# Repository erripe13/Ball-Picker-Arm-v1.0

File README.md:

#  Bras Robotisé attrapeur de balles

Ce projet est un bras robotisé classique à deux axes + une pince, destiné à attraper une balle grâce à une vision basée sur OpenCV.
Ce repository contient l'ensemble du code source ainsi que la CAO du shield Arduino.

## Principe et matériel

Ce projet est basé sur un **Raspberry Pi 4** (2GB RAM) muni de sa **Pi Caméra v2**, exécutant le code Python pour la détection de la balle, et transmettant par USB à l'**Arduino** les coordonnées de cette balle. L'Arduino est chargée de commander le **moteur pas-à-pas** de translation et les deux **servomoteurs** de commande du bras robotisé de manière à ce qu'il attrape la balle en question.

Un Shield Arduino conçu pour ce projet, dont la CAO est disponible dans le dossier [Shield PCB](https://github.com/erripe13/Ball-Picker-Arm-v1.0/tree/main/Shield%20PCB).  Il permet de connecter à l'Arduino, mais surtout d'alimenter, tous les périphériques du projet (hormis la caméra, l'interrupteur DEBUG, et le ruban led qui sont directement connectés au Raspberry Pi) à savoir :
 - Capteur fin de course de translation (calibration de l'axe X)
 - Capteur de température (régulation de la ventilation) (5V)
 - Ventilateurs (12V input, sortie variable par pwm)
 - Servomoteur fort couple n°1 (6V)
 - Servomoteur fort couple n°2 (6V)
 - Servomoteur de la pince (5V)
 - Driver du moteur pas-à-pas (12V)

Ce Shield comporte aussi deux circuits de coupure d'alimentation des moteurs par deux MOSFET (n et p, IRL510 et IRF4905) en montage high-side. Cela permet de "reposer" les servomoteurs quand ils ne servent pas pour éviter la surchauffe. Un MOSFET-N est également utilisé en montage low-side pour réguler l'alimentation des ventilateurs. Les détails et la schématique de cette carte sont disponibles dans le dossier du projet KiCad précédemment cité.

## Rôle des programmes - arborescence du dépôt

À la racine sont disponibles les programmes Python destinés à être exécutés sur le Raspberry Pi. 

 - *ball_tracking* est le programme principal, il remplit les fonctions suivantes :
	 - détection de la balle par filtrage HSV puis détection de contours
	 - compensation de la perspective dûe à l'orientation non-zénitale de la caméra
	 - extraction des coordonnées réelles de la balle
	 - envoi des coordonnées à l'Arduino par USB une fois la balle immobile
 - *hsv_define* permet de définir manuellement les seuils (bas et haut) de chaque paramètre du filtre HSV (cf. tuto plus bas dans ce document)
 - *NeoPixel* est exécuté au démarrage du système et allume en blanc le ruban LED connecté au GPIO18 du Raspberry

Dans le dossier arduino_runrobot on trouve le programme unique exécuté par l'Arduino

 - *arm_arduino.ino* permet d'effectuer les tâches suivantes :
	 - réception de décodage des coordonnées de la balle
	 - pilotage des moteurs pour se déplacer et aller attraper la balle

## Procédure de calibration

### Calibration du trapèze de détection - correction de la perspective

La calibration de la correction de perspective a été réduite au plus simple. Pour y accéder, il faut démarrer le système avec le switch DEBUG activé. On dispose ainsi d'un affichage de la vidéo avant traitement :
L'objectif est de régler manuellement la position de la caméra pour faire coincider les points rouges avec les quatre angles du plateau de jeu. 

Une fois cette tâche réalisée on peut basculer le bouton debug en position normale et observer l'image après son traitement, par conséquent rectifiée.

Si on souhaite modifier les coordonnées de ces points (attention : ce n'est pas nécessaire dans la situation du modèle actuel du robot) il s'agit des lignes 70 à 75 du programme *ball_tracking* :

    #affichage des points rouges
    calib = cv2.circle(frame,(84,38), 5,(0,0,255),-1)
    calib = cv2.circle(calib,(449,36),5,(0,0,255),-1)
    calib = cv2.circle(calib,(34,419),5,(0,0,255),-1)
    calib = cv2.circle(calib,(517,415),5,(0,0,255),-1)
    #déclaration des points du trapèze à rectifier (identiques au points rouges, respecter l'ordre)
    imgPts = np.float32([[84,38],[449,36],[34,419],[517,415]])

### Calibration du filtre de couleur  - détection de la balle

Si la balle n'est pas correctement détectée, où qu'on souhaite utiliser une autre couleur de balle, il est nécessaire de trouver les 6 seuils de réglage du filtre.
Il faut exécuter le programme *hsv_define*. On y observe le flux caméra sans filtrage, puis une autre fenêtre avec 6 sliders et la sortie du filtre juste en-dessous.

Il faut d'abord cherche les 3 meilleurs paramètres LOW dans l'ordre HSV pour que la sortie du filtre soit la plus propre possible, puis ensuite diminuer les 3 paramètres HIGH pour nettoyer au mieux le reste de pollution. La sortie du filtre doit afficher en blanc la balle, quasiment sans aucune autre perturbation. Une fois ces 6 paramètres trouvés, il faut les renseigner dans le programme _ball_tracking_ au lignes 23 et 24.

    HSVLower = (15, 112, 143) #(H low, S low, V low)
    HSVUpper = (45, 255, 255) #(H up, S up, V up)

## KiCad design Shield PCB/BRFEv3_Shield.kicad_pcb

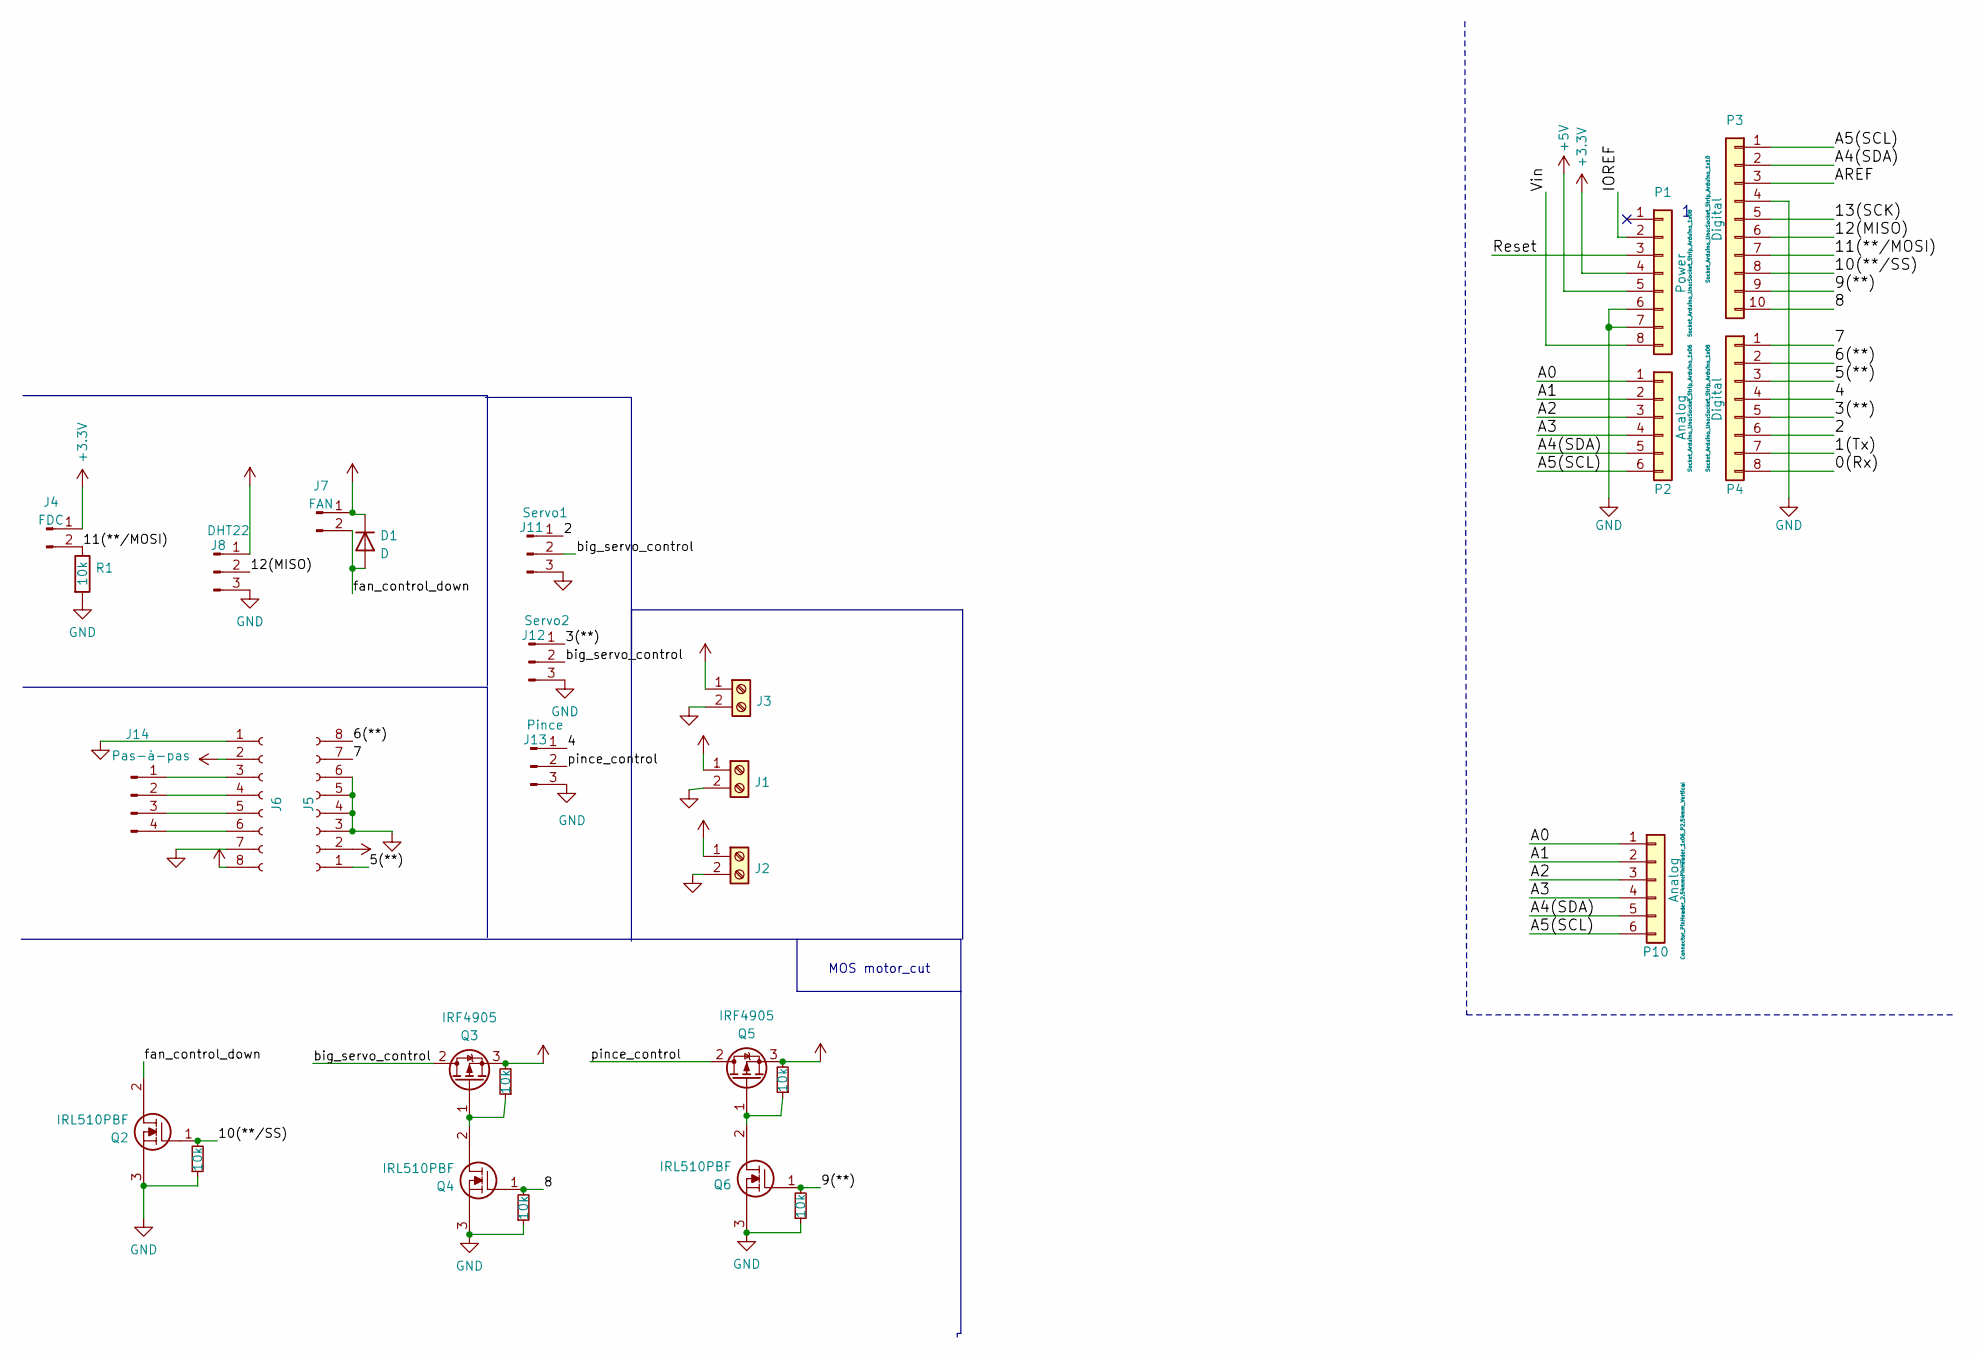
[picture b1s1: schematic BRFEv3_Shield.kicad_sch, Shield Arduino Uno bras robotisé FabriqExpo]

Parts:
D1: D; D_DO-41_SOD81_P3.81mm_Vertical_AnodeUp
J1, J2, J3: Screw_Terminal_01x02; PhoenixContact_MSTBVA_2,5_2-G_1x02_P5.00mm_Vertical
J4: FDC; PinHeader_1x02_P2.54mm_Vertical
J5, J6: Conn_01x08_Female; PinHeader_1x08_P2.54mm_Vertical
J7: FAN; PinHeader_1x02_P2.54mm_Vertical
J8: DHT22; PinHeader_1x03_P2.54mm_Vertical
J11: Servo1; PinHeader_1x03_P2.54mm_Vertical
J12: Servo2; PinHeader_1x03_P2.54mm_Vertical
J13: Pince; PinHeader_1x03_P2.54mm_Vertical
J14: Pas-à-pas; PinHeader_1x04_P2.54mm_Vertical
P1: Power; Socket_Strip_Arduino_1x08
P2: Analog; Socket_Strip_Arduino_1x06
P3: Digital; Socket_Strip_Arduino_1x10
P4: Digital; Socket_Strip_Arduino_1x08
P10: Analog; PinHeader_1x06_P2.54mm_Vertical
Q2, Q4, Q6: IRL510PBF; TO-220-3_Vertical; Manufacturer_Part_Number IRL510PBF; Mouser Part Number 844-IRL510PBF
Q3, Q5: IRF4905; TO-220-3_Vertical
R1, R3, R4, R5, R6, R7: 10k; R_Axial_DIN0204_L3.6mm_D1.6mm_P5.08mm_Vertical

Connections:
+3V3: J4.1, P1.4
+5V: J2.1, J5.2, J6.2, J8.1, P1.5, Q5.3 (S), R6.2
+6V: J1.1, Q3.3 (S), R4.2
+12V: D1.1 (K), J3.1, J6.8, J7.1
/0(Rx): P4.8
/1(Tx): P4.7
/2: J11.1, P4.6
/3(**): J12.1, P4.5
/4: J13.1, P4.4
/5(**): J5.1, P4.3
/6(**): J5.8, P4.2
/7: J5.7, P4.1
/8: P3.10, Q4.1, R5.2
/9(**): P3.9, Q6.1, R7.2
/12(MISO): J8.2, P3.6
/13(SCK): P3.5
/A0: P2.1, P10.1
/A1: P2.2, P10.2
/A2: P2.3, P10.3
/A3: P2.4, P10.4
/A4(SDA): P2.5, P3.2, P10.5
/A5(SCL): P2.6, P3.1, P10.6
/AREF: P3.3
/IOREF: P1.2
/Reset: P1.3
/Vin: P1.8
/big_servo_control: J11.2, J12.2, Q3.2 (D)
/fan_control_down: D1.2 (A), J7.2, Q2.2
/pince_control: J13.2, Q5.2 (D)
GND: J1.2, J2.2, J3.2, J5.3, J5.4, J5.5, J5.6, J6.1, J6.7, J8.3, J11.3, J12.3, J13.3, P1.6, P1.7, P3.4, Q2.3, Q4.3, Q6.3, R1.2, R3.1, R5.1, R7.1
unnamed: J6.3, J14.1
unnamed: J6.4, J14.2
unnamed: J6.5, J14.3
unnamed: J6.6, J14.4
unnamed: Q3.1 (G), Q4.2, R4.1
unnamed: Q5.1 (G), Q6.2, R6.1

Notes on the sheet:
MOS motor_cut

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
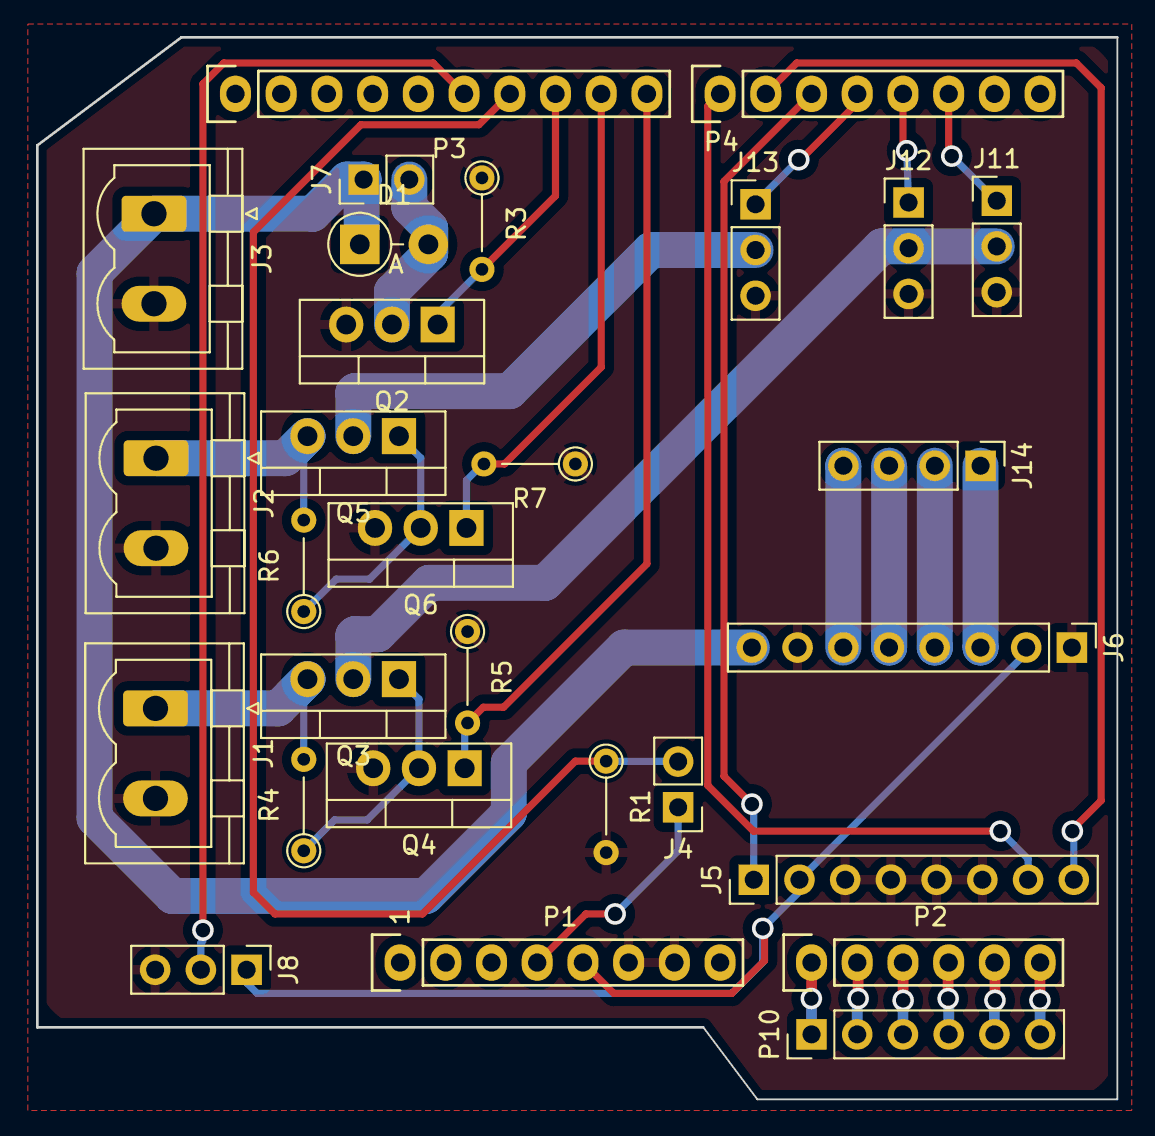
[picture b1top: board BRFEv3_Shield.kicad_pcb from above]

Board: 2 copper layers, 60.0 x 59.0 mm, 29 parts (0 on the bottom side), 31 nets.

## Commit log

2022-04-26 first push
    updated opencv and whole working code
2022-04-29 pi commit
2022-04-29 ball track
2022-05-10 gitignore
2022-05-11 +cao
2022-05-11 updatecao
2022-05-11 cao update
2022-05-11 update cao
2022-05-14 shield update
2022-05-14 Arduino script
2022-05-16 Arduino update
2022-05-16 update commentaires
2022-05-17 correction altium
2022-05-18 mise à jour gui test py3
2022-05-19 update programmes d'essai
2022-05-19 update calib distorsion
2022-05-19 update calib
2022-05-20 test
2022-05-20 test programs update
2022-05-24 update calib img
2022-05-24 up calib img
2022-05-24 calib up
2022-05-24 update correc arduino
2022-05-24 data disto
2022-05-24 update festival
2022-05-25 calib update
2022-05-25 update test mod
2022-05-25 mise au point
2022-05-28 upload calib
2022-05-28 pointloc
2022-05-28 capture
2022-05-28 updateperspec
2022-05-28 update calib intrisèque
2022-05-30 update arduino
2022-05-30 updatea rduino
2022-06-02 update general
2022-06-02 source main
2022-06-02 nouvelle proposition
2022-06-07 backup
2022-06-13 update servo offset
2022-06-13 update servo
2022-06-16 update shield
2022-06-17 update calib+cao
2022-06-17 calibopti
2022-06-20 update cao+calib
2022-06-23 add fancontrol
2022-06-23 added proportional fan control
2022-06-23 update new arm + RGB
2022-06-25 wqsx
2022-06-26 update opti
2022-07-04 update cam
2022-07-05 transform
2022-07-05 tracking update with cm coordinates
2022-07-05 update_debug_vision
2022-07-05 update stop ball
2022-07-05 update ball tracking
2022-07-05 add_main
2022-07-05 updaterobot
2022-07-05 correction
2022-07-05 add bckp
2022-07-05 updt
2022-07-05 newlayout
2022-07-05 update behavior
2022-07-06 add_led
2022-07-06 version2
2022-07-06 endstop
2022-07-06 correct
2022-07-06 stepper OK main
2022-07-06 update command
2022-07-06 stepperdest OK
2022-07-06 x to ball OK
2022-07-06 à régler mais fonctionnel
2022-07-06 update précision
2022-07-07 F***ING WORKING
2022-07-07 pre release
2022-07-07 release
2022-07-08 pre-release
2022-07-11 v2.0 release
2022-07-11 Release v1.0
